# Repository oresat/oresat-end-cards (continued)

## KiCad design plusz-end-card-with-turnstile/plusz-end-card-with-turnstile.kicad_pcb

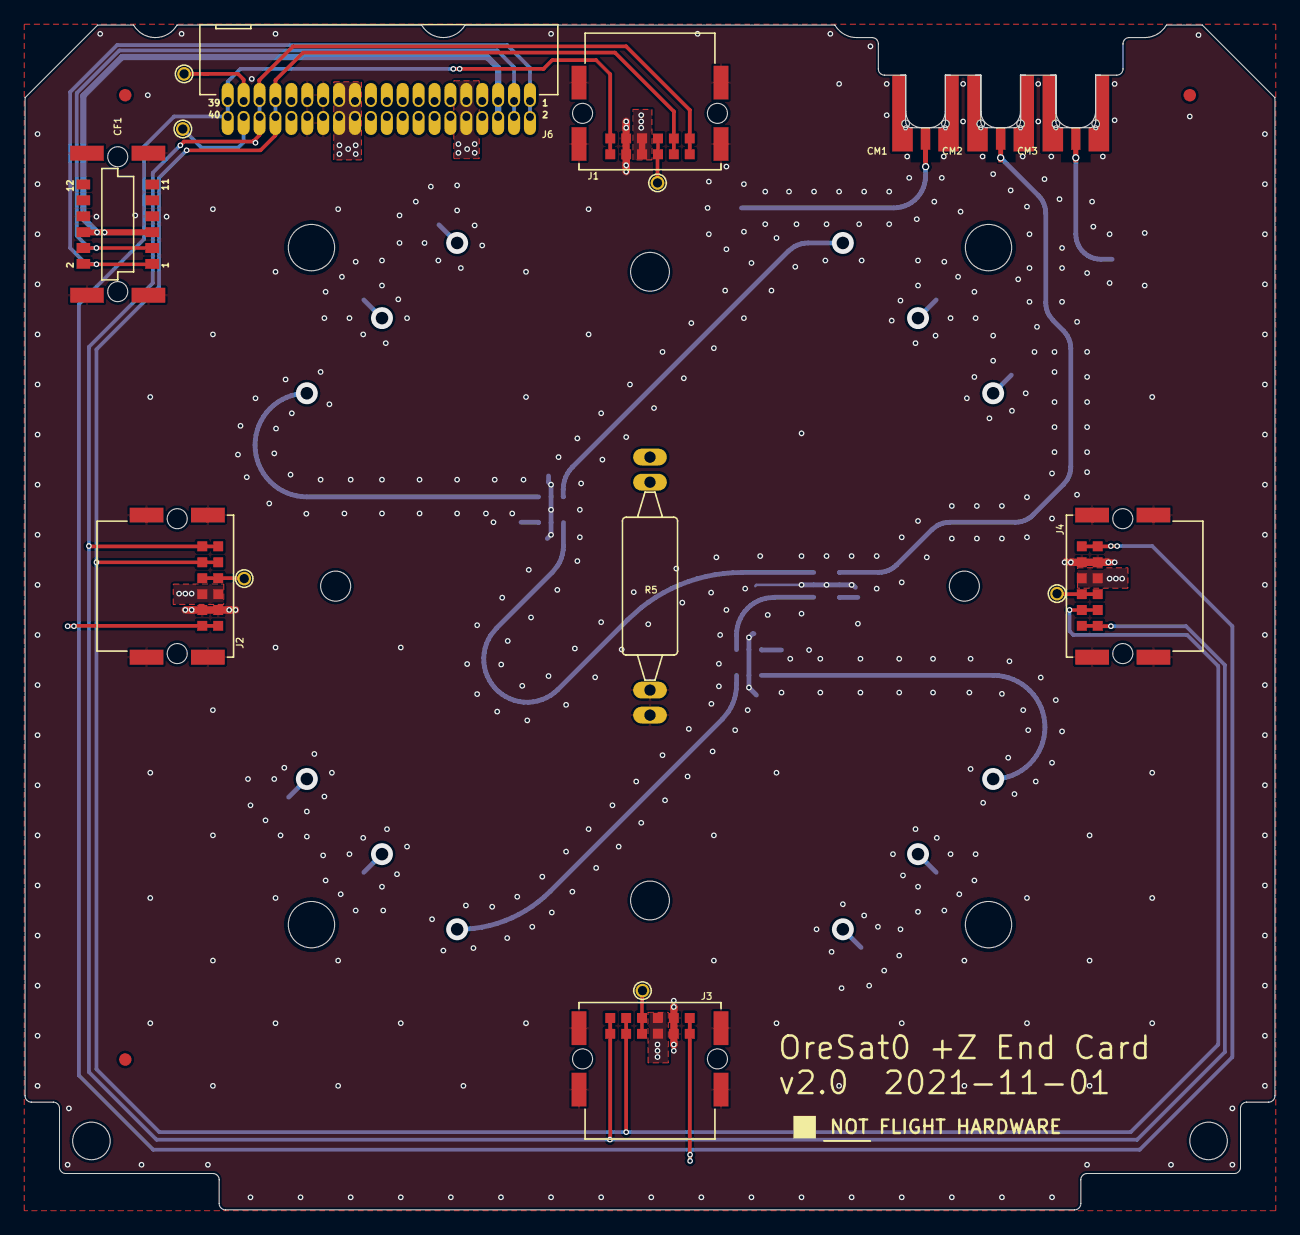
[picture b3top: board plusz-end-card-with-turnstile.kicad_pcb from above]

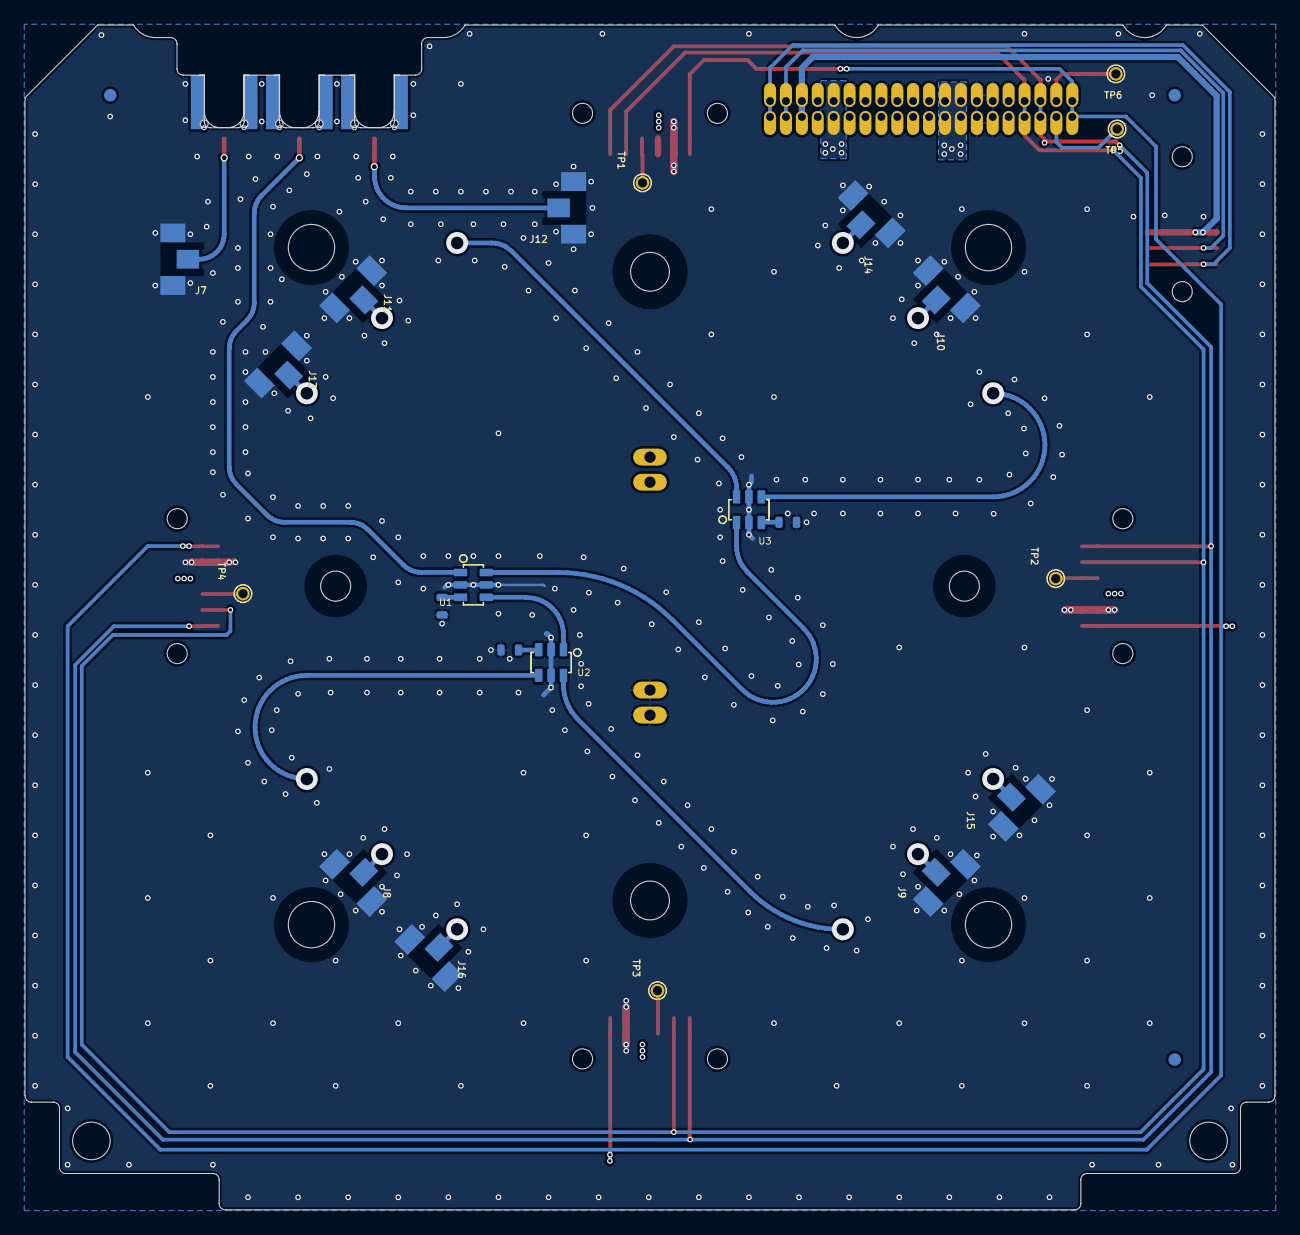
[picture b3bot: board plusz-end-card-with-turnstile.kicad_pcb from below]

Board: 4 copper layers, 99.8 x 94.6 mm, 48 parts (19 on the bottom side), 23 nets.

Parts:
@HOLE0, @HOLE1, @HOLE2, @HOLE3: (no value)
CF1: J-HARWIN-M55-6001242R; HARWIN-M55-60X1242R
CM1, CM2, CM3: J-MOLEX-SMPM-73300-003X; J-MOLEX-SMPM-073300-003X
FIDUCIAL1, FIDUCIAL2, FIDUCIAL3, FIDUCIAL4, FIDUCIAL5, FIDUCIAL6: FIDUCIAL-1.0X2.0
HW1, HW2, HW3, HW4: MCMASTER-94100A150
J1, J2, J3, J4: Harwin M55-7101242R; M55-7101242R
J6: J-SAMTEC-TFM-120-X1-XXX-D-RA
J7, J8, J9, J10, J11, J12, J13, J14, J15, J16: R107064070_CONTACT
PCB1: ORESAT-CARD-V1.3-GENERIC-3RF
R1, R2, R3: 50; .0603-C-NOSILK
R5: 7.5 1W; PAC100-FOR-MELTWIRE
TP1, TP2, TP3, TP4, TP5, TP6: TEST-POINT-LARGE-SQUARE; 1X01
U1, U2, U3: QCN-19+; QCN-XXX+
U$1: FLIGHMARKERNEW; FLIGHTMARKER_NEW_BOARDS

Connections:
C3-UART-RX: J6.38, TP5.1
C3-UART-TX: J6.37, TP6.1
CAN1_H: J1.9, J1.10, J2.9, J2.10, J3.9, J3.10, J4.9, J4.10, J6.33, J6.34
CAN1_L: J1.11, J1.12, J2.11, J2.12, J3.11, J3.12, J4.11, J4.12, J6.35, J6.36
GND: CF1.7, CF1.8, CF1.P$1, CF1.P$2, CF1.P$3, CF1.P$4, J1.3, J1.4, J1.P$1, J1.P$2, J1.P$3, J1.P$4, J2.3, J2.4, J2.P$1, J2.P$2, J2.P$3, J2.P$4, J3.3, J3.4, J3.P$1, J3.P$2, J3.P$3, J3.P$4, J4.3, J4.4, J4.P$1, J4.P$2, J4.P$3, J4.P$4, J6.27, J6.28, J6.29, J6.30, J7.P$2, J7.P$3, J8.P$2, J8.P$3, J9.P$2, J9.P$3, J10.P$2, J10.P$3, J11.P$2, J11.P$3, J12.P$2, J12.P$3, J13.P$2, J13.P$3, J14.P$2, J14.P$3, J15.P$2, J15.P$3, J16.P$2, J16.P$3, R1.1, R2.1, R3.1, R5.P$1, R5.P$2, U1.2, U1.5, U2.2, U2.5, U3.2, U3.5
L1BAND: CM1.RF, J12.P$1
LBAND: CM2.RF, U1.1
LBAND-1/4L: U1.6, U3.1
LBAND-SHORT: U1.4, U2.1
MAG-POWER: CF1.5, CF1.6, J6.5, J6.6
MAG-SCL: CF1.3, CF1.4, J6.3, J6.4
MAG-SDA: CF1.1, CF1.2, J6.1, J6.2
unnamed: R1.2, U1.3
unnamed: R2.2, U2.3
unnamed: R3.2, U3.3
unnamed: J1.7, J1.8, TP1.1
unnamed: J2.7, J2.8, TP2.1
unnamed: J3.7, J3.8, TP3.1
unnamed: J4.7, J4.8, TP4.1
TURNSTILE-DEPLOY: J6.9, J6.10, R5.P$3, R5.P$4
UHF: CM3.RF, J7.P$1
VBUS: J1.5, J1.6, J2.5, J2.6, J3.5, J3.6, J4.5, J4.6, J6.23, J6.24, J6.25, J6.26
~SD: J1.1, J1.2, J2.1, J2.2, J3.1, J3.2, J4.1, J4.2, J6.39, J6.40
